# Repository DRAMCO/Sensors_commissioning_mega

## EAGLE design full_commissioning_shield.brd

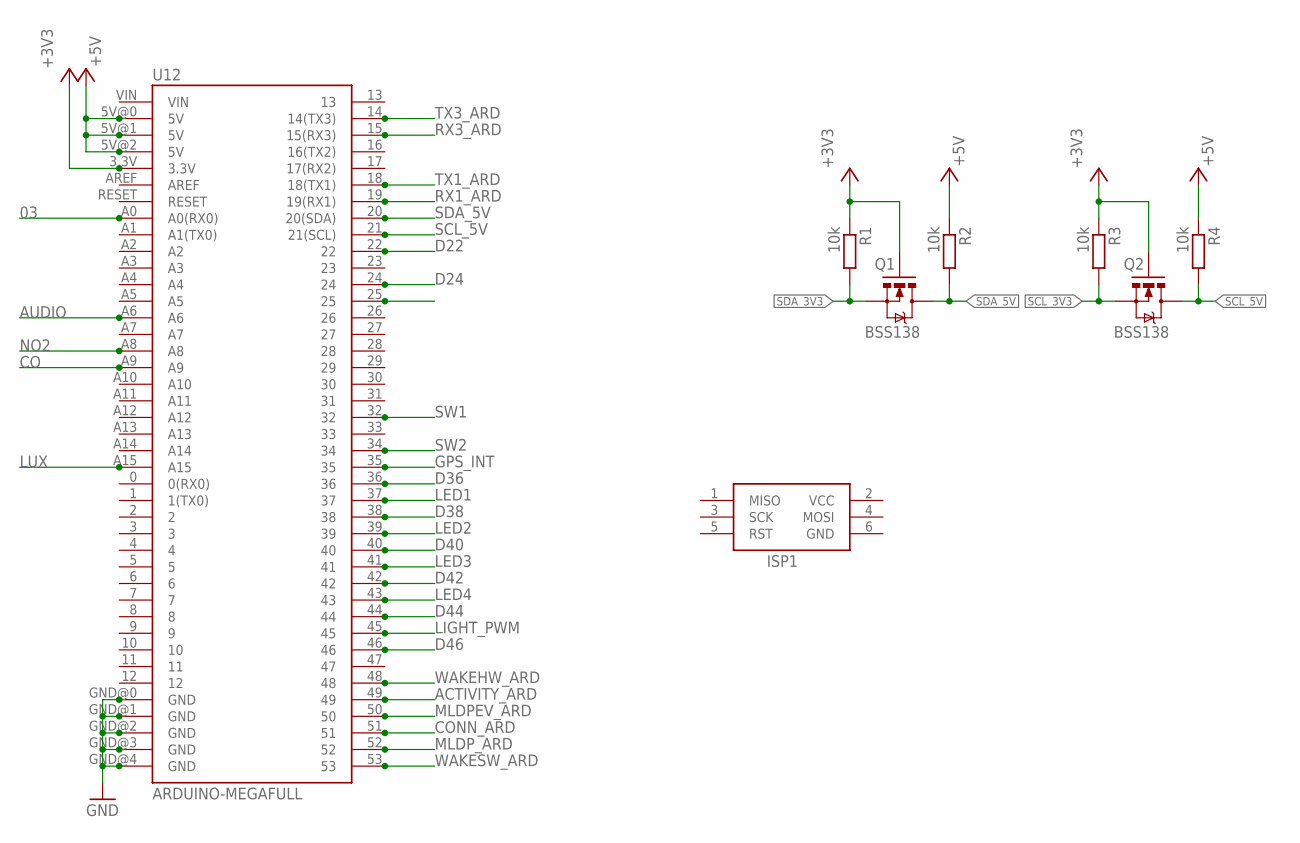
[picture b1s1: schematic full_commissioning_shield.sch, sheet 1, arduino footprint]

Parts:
ISP1: AVRISP-6; AVRISP
Q1, Q2: BSS138; SOT23-3
R1, R2, R3, R4: 10k; R0805
U12: ARDUINO-MEGAFULL; ARDUINO_MEGA

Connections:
03: U12.A0 (A0(RX0)); also elsewhere on the board
+3V3: Q1.1 (G), Q2.1 (G), R1.1, R3.1, U12.3.3V; also elsewhere on the board
+5V: R2.1, R4.1, U12.5V@0 (5V), U12.5V@1 (5V), U12.5V@2 (5V); also elsewhere on the board
ACTIVITY_ARD: U12.49; also elsewhere on the board
AUDIO: U12.A6; also elsewhere on the board
CO: U12.A9; also elsewhere on the board
CONN_ARD: U12.51; also elsewhere on the board
D22: U12.22
D24: U12.24
D36: U12.36; also elsewhere on the board
D38: U12.38; also elsewhere on the board
D40: U12.40; also elsewhere on the board
D42: U12.42; also elsewhere on the board
D44: U12.44; also elsewhere on the board
D46: U12.46; also elsewhere on the board
GND: ISP1.6 (GND), U12.GND@0 (GND), U12.GND@1 (GND), U12.GND@2 (GND), U12.GND@3 (GND), U12.GND@4 (GND); also elsewhere on the board
GPS_INT: U12.35; also elsewhere on the board
LED1: U12.37; also elsewhere on the board
LED2: U12.39; also elsewhere on the board
LED3: U12.41; also elsewhere on the board
LED4: U12.43; also elsewhere on the board
LIGHT_PWM: U12.45; also elsewhere on the board
LUX: U12.A15; also elsewhere on the board
MLDPEV_ARD: U12.50; also elsewhere on the board
MLDP_ARD: U12.52; also elsewhere on the board
NO2: U12.A8; also elsewhere on the board
RX1_ARD: U12.19 (19(RX1))
RX3_ARD: U12.15 (15(RX3)); also elsewhere on the board
SCL_3V3: Q2.2 (S), R3.2; also elsewhere on the board
SCL_5V: Q2.3 (D), R4.2, U12.21 (21(SCL)); also elsewhere on the board
SDA_3V3: Q1.2 (S), R1.2; also elsewhere on the board
SDA_5V: Q1.3 (D), R2.2, U12.20 (20(SDA)); also elsewhere on the board
SW1: U12.32; also elsewhere on the board
SW2: U12.34; also elsewhere on the board
TX1_ARD: U12.18 (18(TX1))
TX3_ARD: U12.14 (14(TX3)); also elsewhere on the board
VCC: ISP1.2 (VCC)
WAKEHW_ARD: U12.48; also elsewhere on the board
WAKESW_ARD: U12.53; also elsewhere on the board

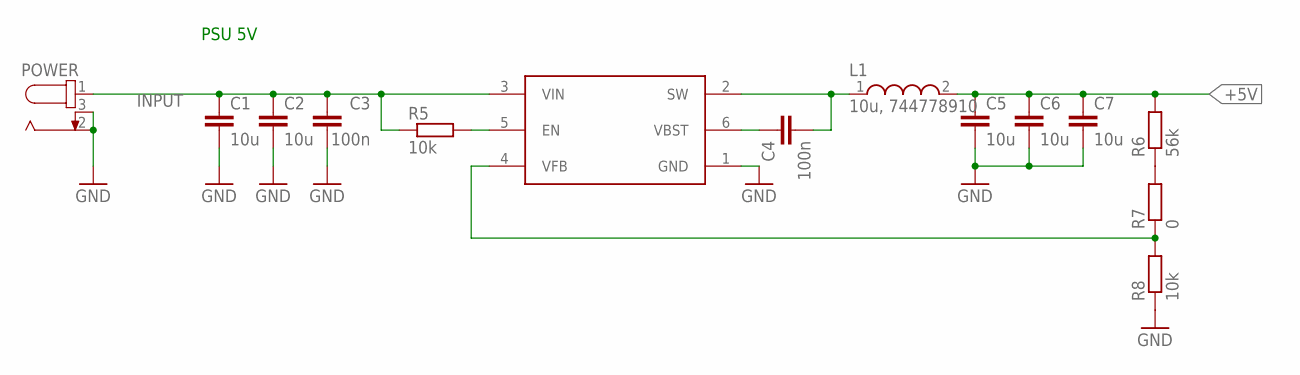
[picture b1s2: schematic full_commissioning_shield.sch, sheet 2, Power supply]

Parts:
C1, C2, C5, C6, C7: 10u; C1206
C3, C4: 100n; C0805
L1: 10u, 744778910; WE-PD_7332/7345
POWER: 694108301002; 69410X301002
R5, R8: 10k; R0805
R6: 56k; R0805
R7: 0; R0805
U13: TPS563200; SOT95P280X145-6N

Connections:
+5V: C5.1, C6.1, C7.1, L1.2, R6.2; also elsewhere on the board
GND: C1.2, C2.2, C3.1, C5.2, C6.2, C7.2, POWER.2, POWER.3, R8.1, U13.1 (GND); also elsewhere on the board
INPUT: C1.1, C2.1, C3.2, POWER.1, R5.1, U13.3 (VIN); also elsewhere on the board
unnamed: R5.2, U13.5 (EN)
unnamed: C4.1, U13.6 (VBST)
unnamed: R6.1, R7.2
unnamed: R7.1, R8.2, U13.4 (VFB)
SW: C4.2, L1.1, U13.2 (SW)

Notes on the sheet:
PSU 5V

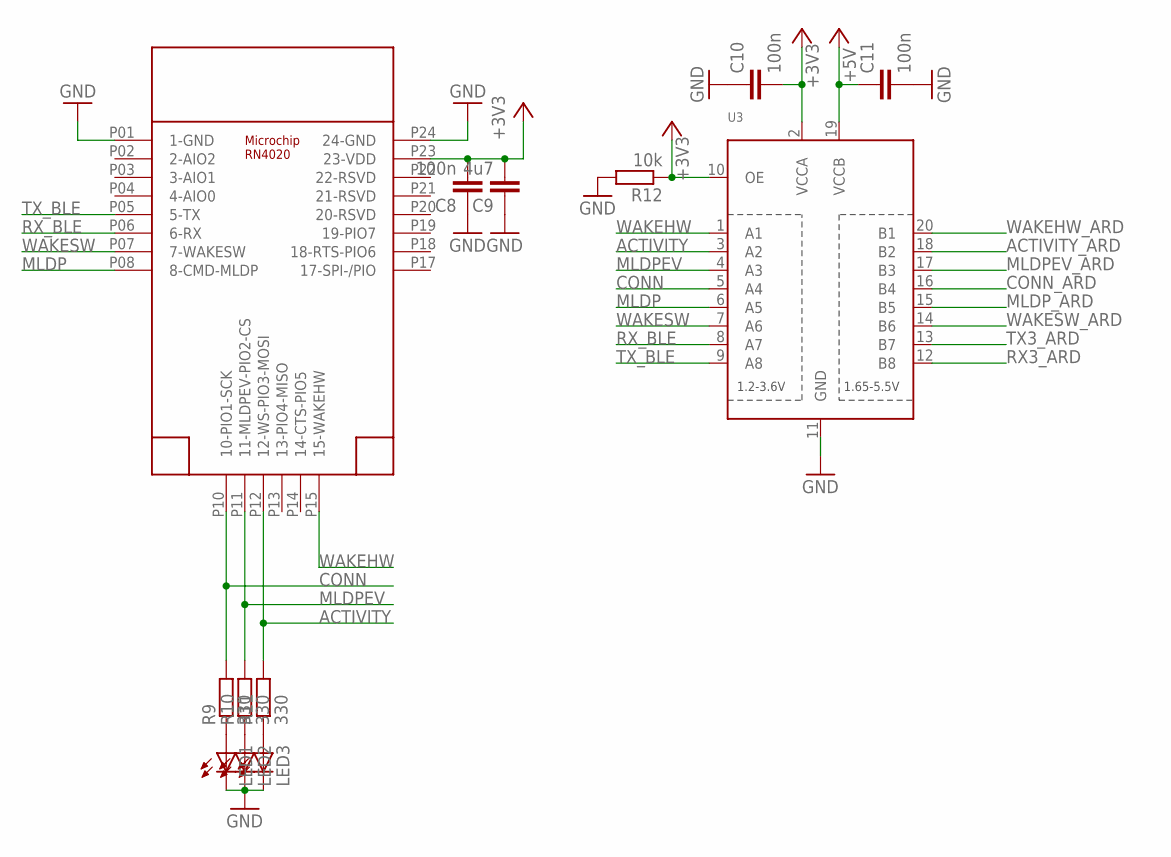
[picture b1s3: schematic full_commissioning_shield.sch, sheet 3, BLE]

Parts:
C8: 100n; C0805K
C9: 4u7; C0805K
C10, C11: 100n; C0805
LED1, LED2, LED3: LEDCHIP-LED0805; CHIP-LED0805
R9, R10, R11: 330; R0805
R12: 10k; R0805
U2: RN4020; RN4020SMD
U3: TXB0108PWR; TSSOP20

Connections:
+3V3: C8.2, C9.2, C10.2, R12.1, U2.P23 (23-VDD), U3.2 (VCCA), U3.10 (OE); also elsewhere on the board
+5V: C11.1, U3.19 (VCCB); also elsewhere on the board
ACTIVITY: R11.2, U2.P12 (12-WS-PIO3-MOSI), U3.3 (A2)
ACTIVITY_ARD: U3.18 (B2); also elsewhere on the board
CONN: R9.2, U2.P10 (10-PIO1-SCK), U3.5 (A4)
CONN_ARD: U3.16 (B4); also elsewhere on the board
GND: C8.1, C9.1, C10.1, C11.2, LED1.C, LED2.C, LED3.C, R12.2, U2.P01 (1-GND), U2.P24 (24-GND), U3.11 (GND); also elsewhere on the board
MLDP: U2.P08 (8-CMD-MLDP), U3.6 (A5)
MLDPEV: R10.2, U2.P11 (11-MLDPEV-PIO2-CS), U3.4 (A3)
MLDPEV_ARD: U3.17 (B3); also elsewhere on the board
MLDP_ARD: U3.15 (B5); also elsewhere on the board
unnamed: LED1.A, R9.1
unnamed: LED2.A, R10.1
unnamed: LED3.A, R11.1
RX3_ARD: U3.12 (B8); also elsewhere on the board
RX_BLE: U2.P06 (6-RX), U3.8 (A7)
TX3_ARD: U3.13 (B7); also elsewhere on the board
TX_BLE: U2.P05 (5-TX), U3.9 (A8)
WAKEHW: U2.P15 (15-WAKEHW), U3.1 (A1)
WAKEHW_ARD: U3.20 (B1); also elsewhere on the board
WAKESW: U2.P07 (7-WAKESW), U3.7 (A6)
WAKESW_ARD: U3.14 (B6); also elsewhere on the board

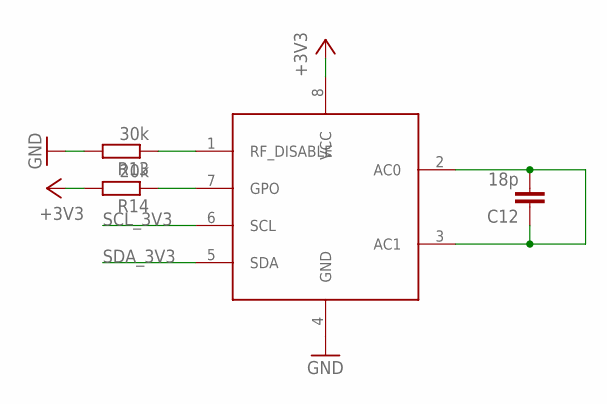
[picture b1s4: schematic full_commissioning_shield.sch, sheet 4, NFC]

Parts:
C12: 18p; C0805K
NFC: M24SR; SO8
R13: 30k; R0805
R14: 20k; R0805

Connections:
+3V3: NFC.8 (VCC), R14.2; also elsewhere on the board
GND: NFC.4 (GND), R13.2; also elsewhere on the board
unnamed: C12.1, C12.2, NFC.2 (AC0), NFC.3 (AC1)
unnamed: NFC.1 (RF_DISABLE), R13.1
unnamed: NFC.7 (GPO), R14.1
SCL_3V3: NFC.6 (SCL); also elsewhere on the board
SDA_3V3: NFC.5 (SDA); also elsewhere on the board

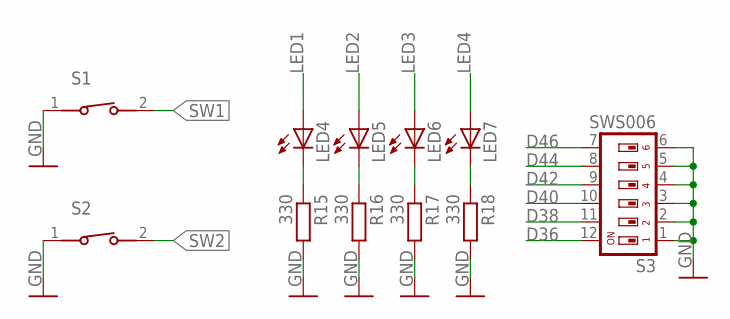
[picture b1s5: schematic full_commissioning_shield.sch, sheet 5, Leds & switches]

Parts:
LED4, LED5, LED6, LED7: LEDCHIP-LED0805; CHIP-LED0805
R15, R16, R17, R18: 330; R0805
S1, S2: 434111043826
S3: SWS006; SMS-006

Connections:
D36: S3.12; also elsewhere on the board
D38: S3.11; also elsewhere on the board
D40: S3.10; also elsewhere on the board
D42: S3.9; also elsewhere on the board
D44: S3.8; also elsewhere on the board
D46: S3.7; also elsewhere on the board
GND: R15.2, R16.2, R17.2, R18.2, S1.1, S2.1, S3.1, S3.2, S3.3, S3.4, S3.5, S3.6; also elsewhere on the board
LED1: LED4.A; also elsewhere on the board
LED2: LED5.A; also elsewhere on the board
LED3: LED6.A; also elsewhere on the board
LED4: LED7.A; also elsewhere on the board
unnamed: LED5.C, R16.1
unnamed: LED4.C, R15.1
unnamed: LED6.C, R17.1
unnamed: LED7.C, R18.1
SW1: S1.2; also elsewhere on the board
SW2: S2.2; also elsewhere on the board

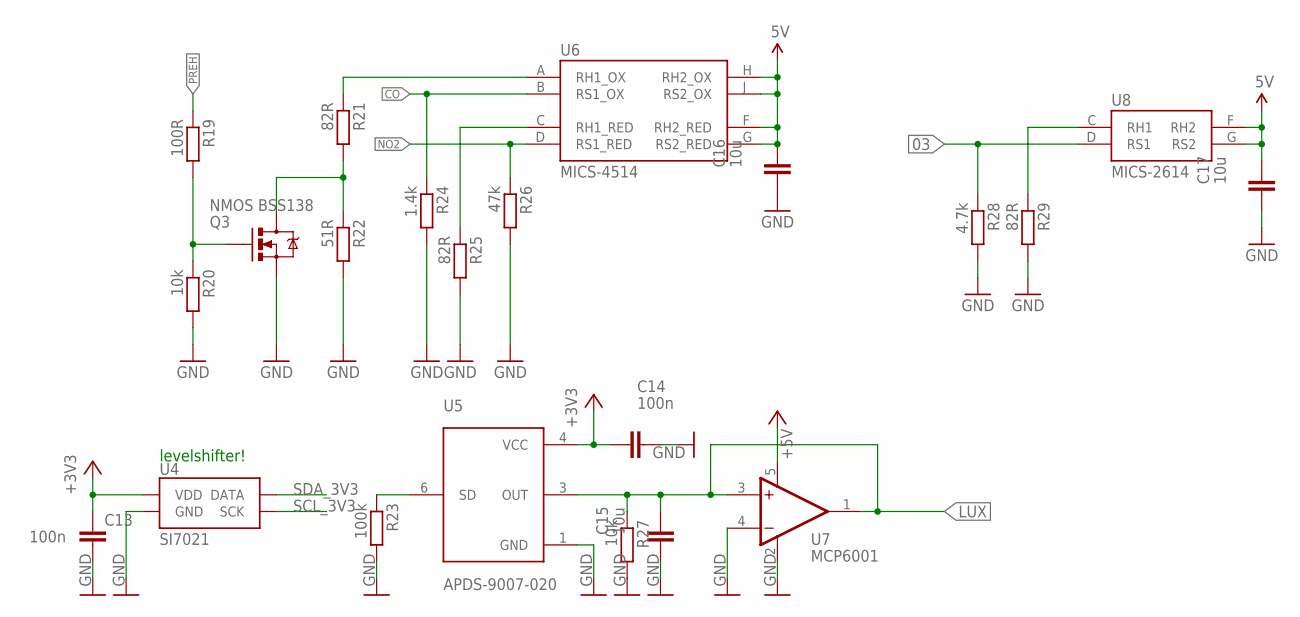
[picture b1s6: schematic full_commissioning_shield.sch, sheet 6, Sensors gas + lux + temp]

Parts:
C13, C14: 100n; C0805
C15, C16, C17: 10u; C0805
Q3: NMOS BSS138; SOT23-3
R19: 100R; R0805
R20, R27: 10k; R0805
R21, R25, R29: 82R; R0805
R22: 51R; R0805
R23: 100k; R0805
R24: 1.4k; R0805
R26: 47k; R0805
R28: 4.7k; R0805
U4: SI7021
U5: APDS-9007-020; LCC140P200X240X80-6
U6: MICS-4514; MICS_10-SMD
U7: MCP6001; SOT23-5
U8: MICS-2614; MICS_10-SMD

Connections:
03: R28.1, U8.D (RS1); also elsewhere on the board
+3V3: C13.2, C14.2, U4.VDD, U5.4 (VCC); also elsewhere on the board
+5V: C16.1, C17.1, U6.F (RH2_RED), U6.G (RS2_RED), U6.H (RH2_OX), U6.J (RS2_OX), U7.5 (V+), U8.F (RH2), U8.G (RS2); also elsewhere on the board
CO: R24.1, U6.B (RS1_OX); also elsewhere on the board
GND: C13.1, C14.1, C15.2, C16.2, C17.2, Q3.2 (S), R20.2, R22.2, R23.2, R24.2, R25.2, R26.2, R27.2, R28.2, R29.2, U4.GND, U5.1 (GND), U7.2 (V-), U7.4 (-IN); also elsewhere on the board
LUX: C15.1, R27.1, U5.3 (OUT), U7.1 (OUT), U7.3 (+IN); also elsewhere on the board
unnamed: R23.1, U5.6 (SD)
unnamed: Q3.3 (D), R21.2, R22.1
unnamed: Q3.1 (G), R19.2, R20.1
unnamed: R21.1, U6.A (RH1_OX)
unnamed: R25.1, U6.C (RH1_RED)
unnamed: R29.1, U8.C (RH1)
NO2: R26.1, U6.D (RS1_RED); also elsewhere on the board
PREH: R19.1
SCL_3V3: U4.SCK; also elsewhere on the board
SDA_3V3: U4.DATA; also elsewhere on the board

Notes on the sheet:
levelshifter!

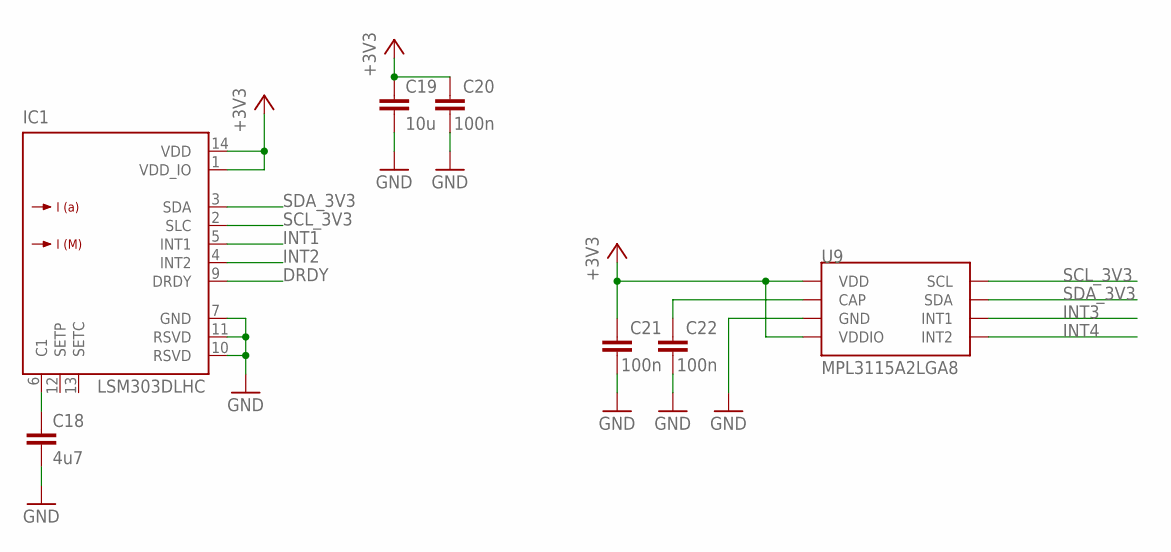
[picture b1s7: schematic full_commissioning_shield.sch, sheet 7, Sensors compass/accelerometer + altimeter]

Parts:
C18: 4u7; C0805
C19: 10u; C0805
C20, C21, C22: 100n; C0805
IC1: LSM303DLHC; LGA-14
U9: MPL3115A2LGA8; LGA8

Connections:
+3V3: C19.1, C20.2, C21.2, IC1.1 (VDD_IO), IC1.14 (VDD), U9.1 (VDD), U9.4 (VDDIO); also elsewhere on the board
DRDY: IC1.9 (DRDY)
GND: C18.2, C19.2, C20.1, C21.1, C22.1, IC1.7 (GND), IC1.10 (RSVD), IC1.11 (RSVD), U9.3 (GND); also elsewhere on the board
INT1: IC1.5 (INT1)
INT2: IC1.4 (INT2)
INT3: U9.6 (INT1)
INT4: U9.5 (INT2)
unnamed: C18.1, IC1.6 (C1)
unnamed: C22.2, U9.2 (CAP)
SCL_3V3: IC1.2 (SLC), U9.8 (SCL); also elsewhere on the board
SDA_3V3: IC1.3 (SDA), U9.7 (SDA); also elsewhere on the board

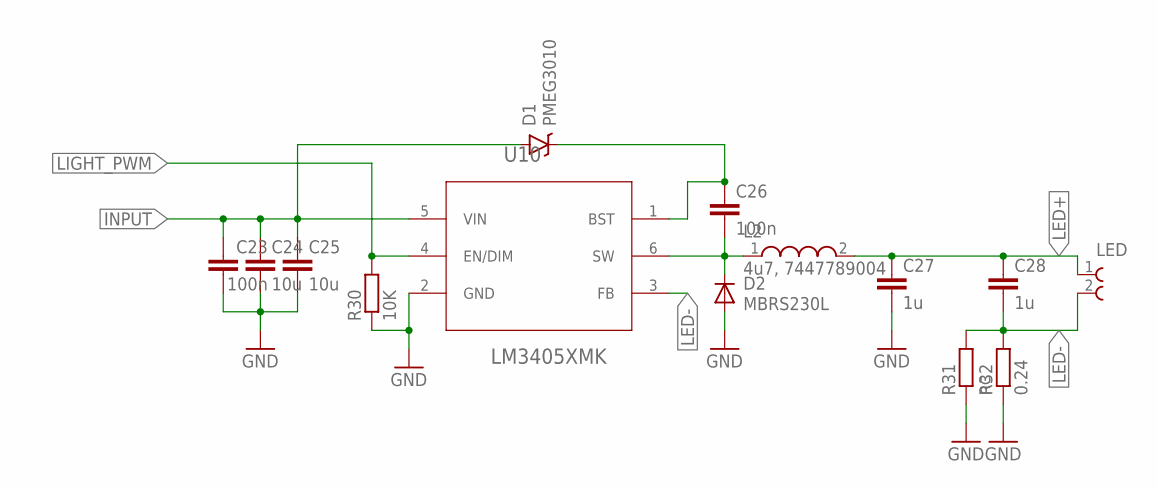
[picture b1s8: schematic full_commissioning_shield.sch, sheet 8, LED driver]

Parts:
C23, C26: 100n; C0805
C24, C25: 10u; C1206
C27, C28: 1u; C0805
D1: PMEG3010; SOD-323
D2: MBRS230L; SMB
L2: 4u7, 7447789004; WE-PD_7332/7345
LED: 691236510002
R30: 10K; R0805
R31: nc; R1206
R32: 0.24; R1206
U10: LM3405XMK; SOT95P285X100-6N

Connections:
GND: C23.1, C24.2, C25.2, C27.2, D2.A, R30.1, R31.1, R32.1, U10.2 (GND); also elsewhere on the board
INPUT: C23.2, C24.1, C25.1, D1.A, U10.5 (VIN); also elsewhere on the board
LED+: C27.1, C28.1, L2.2, LED.1
LED-: C28.2, LED.2, R31.2, R32.2, U10.3 (FB)
LIGHT_PWM: R30.2, U10.4 (EN/DIM); also elsewhere on the board
unnamed: C26.2, D2.C, L2.1, U10.6 (SW)
unnamed: C26.1, D1.C, U10.1 (BST)

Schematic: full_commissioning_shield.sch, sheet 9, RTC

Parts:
U11: DS1342U+; SOP65P490X110-8N
Y1: ABS07-32.768KHZ-T; CM7V-T1A

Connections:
+5V: U11.8 (VCC); also elsewhere on the board
GND: U11.4 (GND); also elsewhere on the board
unnamed: U11.2 (X2), Y1.P$1
unnamed: U11.1 (X1), Y1.P$2
RTC_INTA: U11.3 (CLKIN/~INTA)
RTC_INTB: U11.7 (SQW/~INTB)
SCL_5V: U11.6 (SCL); also elsewhere on the board
SDA_5V: U11.5 (SDA); also elsewhere on the board

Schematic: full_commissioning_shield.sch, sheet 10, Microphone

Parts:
C29: 10n; C0805
C30: 22p; C0805
C31, C33, C36: 100n; C0805
C32: 1n; C0805
C34, C35: 1u; C0805
IC2: TLV341A; SC70-6L
MIC: ICS40310
R33, R36: 120k; R0805
R34: 10k; R0805
R35: 580k; R0805
R37: 39k; R0805
U14: MIC5365; SOT95P280X100-5N

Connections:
1.2V: C35.2, C36.2, MIC.VDD, U14.VOUT
5V: IC2.5 (!SHDN)
+3V3: C33.2, C34.2, R33.1, R34.1, R36.1, U14.EN, U14.VIN; also elsewhere on the board
+5V: IC2.6 (V+); also elsewhere on the board
AUDIO: C32.2, R37.1; also elsewhere on the board
GND: C32.1, C33.1, C34.1, C35.1, C36.1, IC2.2 (V-), MIC.GND, U14.GND; also elsewhere on the board
unnamed: C29.1, MIC.OUT
unnamed: C29.2, IC2.1 (+IN), R33.2
unnamed: C30.1, IC2.3 (-IN), R34.2, R35.1
unnamed: C30.2, C31.1, IC2.4 (OUT), R35.2
unnamed: C31.2, R36.2, R37.2

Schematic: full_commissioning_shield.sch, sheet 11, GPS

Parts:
C37: 100n; C0805
C38: 1u; C0805
GPS: TITAN X1 GPS; TITAN_X1_GPS
JP1: MOLEX734120110; MICROCOAXIAL
L3: 600Ohm/100MHz; 0603
R38, R39: 10K; R0805

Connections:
!RESET: GPS.22 (!RESET), R39.1
+3V3: L3.1, R38.2, R39.2; also elsewhere on the board
GND: C37.1, C38.1, GPS.1 (GND), GPS.3 (GND), GPS.4 (GND), GPS.5 (GND), GPS.6 (GND), GPS.9 (GND), GPS.10 (GND), GPS.11 (GND), GPS.24 (GND), JP1.GND1, JP1.GND2, JP1.GND3; also elsewhere on the board
GPS_INT: GPS.16 (INT); also elsewhere on the board
GPS_PPS: GPS.21 (1PPS)
GPS_WAKEUP: GPS.12 (WAKE_UP), R38.1
unnamed: C37.2, C38.2, GPS.7 (VCC), L3.2
unnamed: GPS.2 (EX_ANT), JP1.SIGNAL (ANT)
SCL_3V3: GPS.14 (SCL); also elsewhere on the board
SDA_3V3: GPS.13 (SDA); also elsewhere on the board

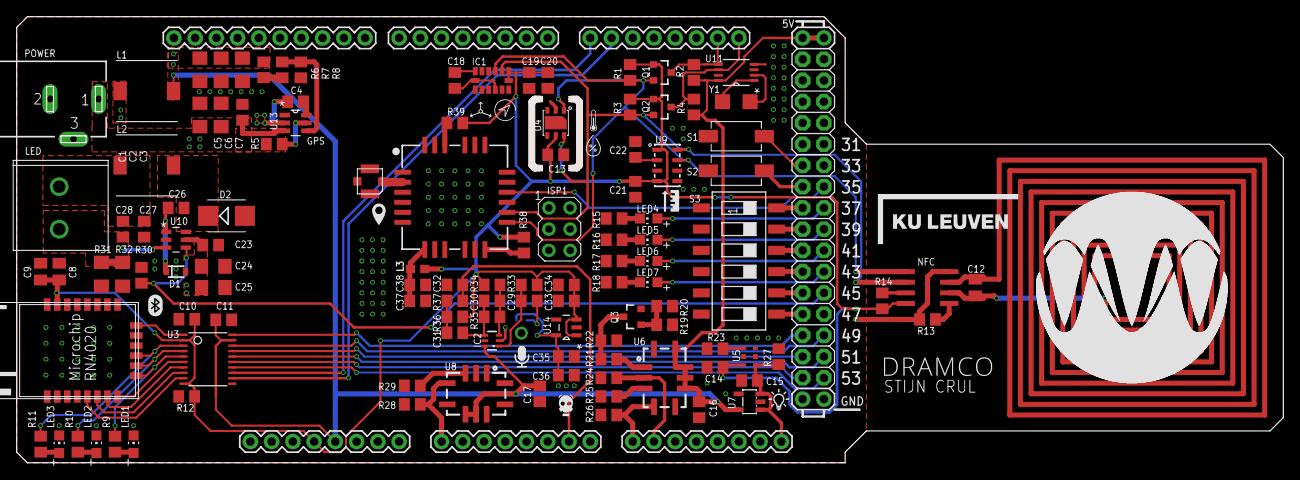
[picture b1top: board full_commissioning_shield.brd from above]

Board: 2 copper layers, 150.6 x 52.5 mm, 118 parts (1 on the bottom side), 82 nets.

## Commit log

2017-07-19 First commit
    First version of Arduino mega shield with a variaty of senors to research their use for comissioning.
2017-08-03 Fixed some errors
    - Fixed a missing net
    - Minor polygon fixes
2017-08-03 Updated gerber files
2017-08-04 Fixed footprint
    Fixed Arduino Mega footprint and updated gerber files
2017-08-14 Minor fixes
    Power connector + polygons

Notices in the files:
parts and their libraries:
SparkFun-Boards: Licensing: Creative Commons ShareAlike 4.0 International - https://creativecommons.org/licenses/by-sa/4.0
EagleLibrary_Wuerth_Elektronik_eiSos_rev: Copyright: Würth Elektronik
